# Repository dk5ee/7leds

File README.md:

## LEDs with Software PWM

X-axis: Time; Y-axis: PWM-value

#### Normal Hardware PWM

#### SoftwarePWM, with prime distribution

#### Delta Modulation/DPCM distribution

### Content of Repository

This repository comprises of this parts: 
1. Code for AVR Microcontroller to light up attached LEDs
2. Code for sending commands to the Microcontroller
3. Extra design files

### Microcontroller Code

Atmega328 modules with optiboot/arduino bootlader and USB serial are used.

Not quite PWM, as the uptime of the outputs are distributed over time.

the main.c in "code" uses 8 bit generation with "prime"-algorithm for seven LEDs/outputs

for comparison:

the main.c in "code2" uses 8 bit generation with "synthetic division"-algorithm for seven LEDs/outputs, which is equivalent to Delta Modulation / Differential pulse-code modulation (DPCM)

for further experiments:

the main.c in "code3" uses 16 bit generation with  "prime"-algorithm for just one LED/output

### Command Code

A Python Project in "webserver" allows commanding the controller over webinterface

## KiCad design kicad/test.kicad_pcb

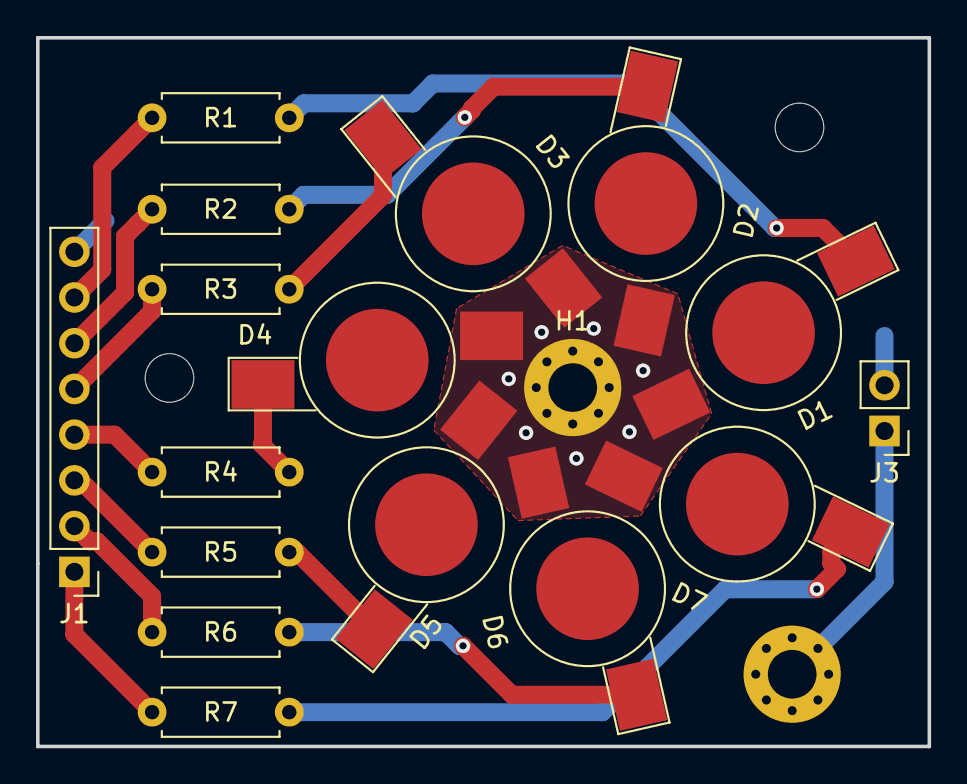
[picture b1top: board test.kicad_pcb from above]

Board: 2 copper layers, 49.5 x 39.4 mm, 20 parts (0 on the bottom side), 16 nets.

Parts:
D1, D2, D3, D4, D5, D6, D7: LED; LED_1W_3W_R8
H1, H2: pad; MountingHole_2.7mm_M2.5_Pad_Via
H3, H4: _; MountingHole_2.7mm_M2.5
J1: uln; PinHeader_1x08_P2.54mm_Vertical
J3: pow; PinHeader_1x02_P2.54mm_Vertical
R1, R2, R3, R4, R5, R6, R7: R; R_Axial_DIN0207_L6.3mm_D2.5mm_P7.62mm_Horizontal

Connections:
GND: H2.1, J3.1
unnamed: D1.1, R1.1
unnamed: D2.1, R2.1
unnamed: D3.1, R3.1
unnamed: D4.1, R4.1
unnamed: D5.1, R5.1
unnamed: D6.1, R6.1
unnamed: D7.1, R7.1
unnamed: J1.1, R7.2
unnamed: J1.2, R6.2
unnamed: J1.3, R5.2
unnamed: J1.4, R4.2
unnamed: J1.5, R3.2
unnamed: J1.6, R2.2
unnamed: J1.7, R1.2
VCC: D1.2, D2.2, D3.2, D4.2, D5.2, D6.2, D7.2, H1.1, J1.8, J3.2

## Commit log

2020-09-25 get code working
2020-09-25 faster pwm
2020-09-25 define interface
2020-09-26 simple webserver
2020-09-26 threaded webserver with long poll
2020-09-27 now with video
2020-09-27 fix firefox problem #1
2020-09-28 cleaning up
2020-09-28 add observers for video
2020-09-28 peanut
2020-09-28 more cleanup
2020-09-28 observer for slider sync
2020-09-28 somethings fishy
2020-09-29 pep8 code style
2020-09-29 different algos
2020-09-29 add readme
2020-09-29 fix markdown
2020-09-29 pictures and description
2020-09-29 typo
2020-10-04 preparing case
2020-10-09 openscad model
2020-10-09 add stubs for colour algorithms
